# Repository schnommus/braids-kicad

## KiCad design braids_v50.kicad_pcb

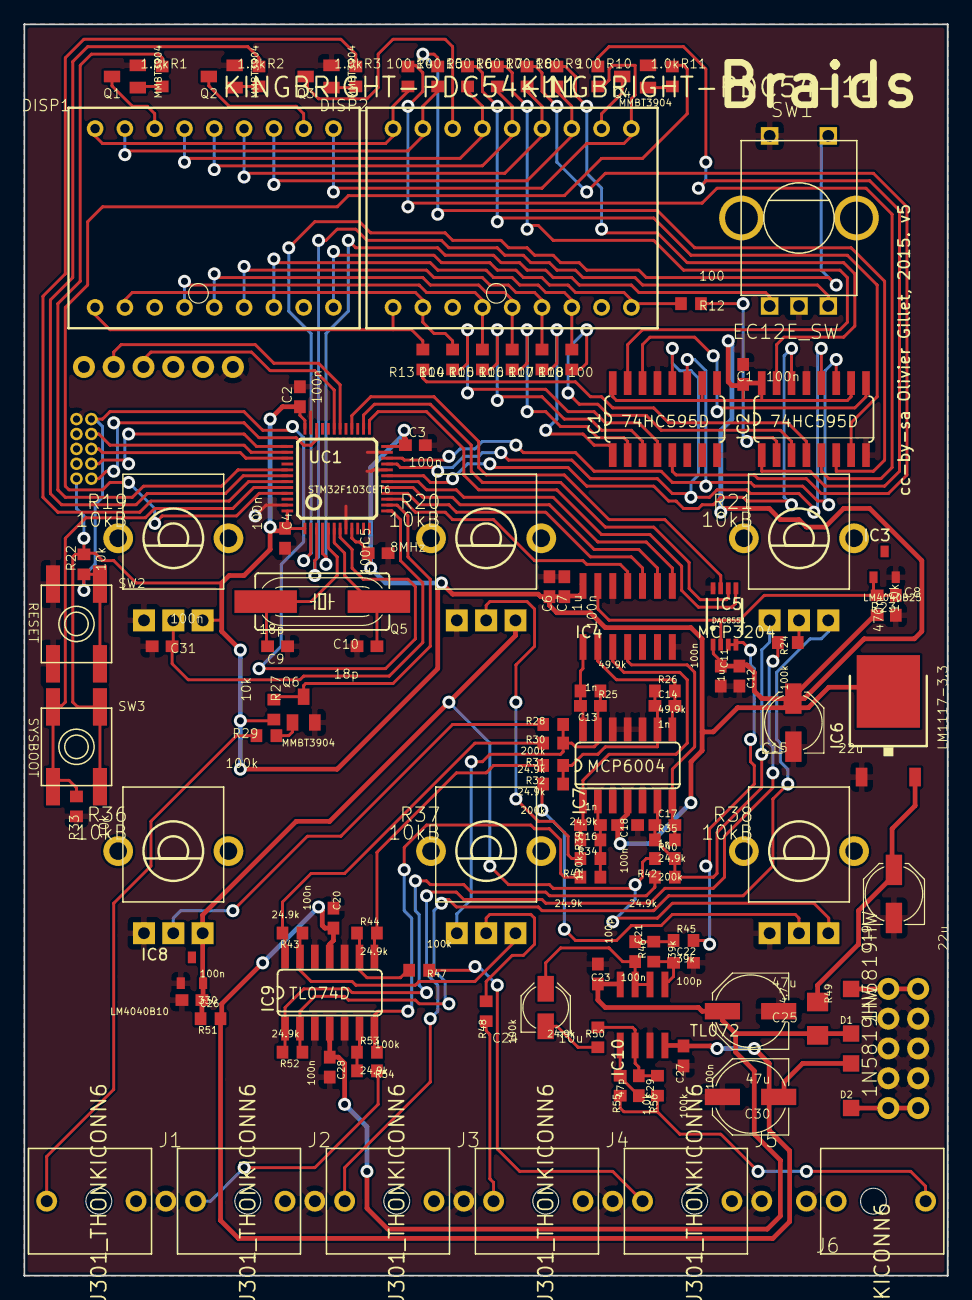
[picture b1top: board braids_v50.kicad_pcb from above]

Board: 2 copper layers, 78.7 x 106.7 mm, 120 parts (0 on the bottom side), 110 nets.

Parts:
C1, C2, C3, C4, C5, C7, C11, C18, C20, C23, C26, C27, C28, C31: 100n; C0603
C6, C12: 1u; C0603
C8: 470n; C0603
C9, C10: 18p; C0603
C13, C14, C16, C17: 1n; C0603
C15, C19: 22u; PANASONIC_C
C21, C22: 100p; C0603
C24: 10u; PANASONIC_B
C25, C30: 47u; PANASONIC_D
C29: 47p; C0603
D1, D2: 1N5819HW; SOD123
DISP1, DISP2: KINGBRIGHT-PDC54-11; PDC54
IC1, IC2: 74HC595D; SO16
IC3: LM4040B25; DBZ_R-PDSO-G3
IC4: MCP3204; SO14
IC5: DAC8551; MSOP-8
IC6: LM1117-3.3; TO252
IC7: MCP6004; SO14
IC8: LM4040B10; DBZ_R-PDSO-G3
IC9: TL074D; SO14
IC10: TL072; SO08
J1, J2, J3, J4, J5, J6: PJ301_THONKICONN6; WQP_PJ_301M6
JP1: M05X2PTH; AVR_ICSP
JP2: M05X2MINIJTAG; 2X5-1.27
JP3: 1X06
Q1, Q2, Q3, Q4, Q6: MMBT3904; SOT23-BEC
Q5: 8MHz; HC49UP
R1, R2, R3, R11, R23, R55: 1.0k; R0603
R4, R5, R6, R7, R8, R9, R10, R12, R13, R14, R15, R16, R17, R18: 100; R0603
R19, R20, R21, R36, R37, R38: 10kB; ALPS_POT_VERTICAL_PS
R22, R27, R33: 10k; R0603
R24, R29, R47, R48, R54, R56: 100k; R0603
R25, R26: 49.9k; R0603
R28, R32, R40: 200k; R0603
R30, R31, R34, R35, R41, R42, R43, R44, R50, R52, R53: 24.9k; R0603
R39: 120k; R0603
R45, R46: 39k; R0603
R49: 4.7; R1206
R51: 330; R0603
SW1: EC12E_SW; ALPS_EC12E_SW
SW2, SW3: EVQ-Q2
UC1: STM32F103CBT6; LQFP48

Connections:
+3V3: C1.1, C2.1, C3.1, C4.1, C5.1, C6.1, C7.1, C11.1, C12.1, C15.+, C18.1, IC1.10, IC1.16, IC2.10, IC2.16, IC4.14, IC5.1, IC6.3, IC7.4, JP2.1, R19.P$1, R22.2, R23.1, R27.2, SW3.B, SW3.B', UC1.1, UC1.9, UC1.24, UC1.36, UC1.48
/braids_v50_SS_1/ADC_MISO: IC4.10, UC1.16
/braids_v50_SS_1/ADC_MOSI: IC4.9, UC1.17
/braids_v50_SS_1/ADC_SCK: IC4.11, UC1.15
/braids_v50_SS_1/ADC_SS: IC4.8, UC1.18
/braids_v50_SS_1/BOOT_FLASH: R33.2, SW3.A, SW3.A', UC1.44
/braids_v50_SS_1/DAC_MOSI: IC5.7, UC1.28
/braids_v50_SS_1/DAC_SCK: IC5.6, UC1.26
/braids_v50_SS_1/DAC_SS: IC5.5, UC1.25
/braids_v50_SS_1/DISP_CHAR0: R3.1, UC1.43
/braids_v50_SS_1/DISP_CHAR1: R11.1, UC1.45
/braids_v50_SS_1/DISP_CHAR2: R1.1, UC1.41
/braids_v50_SS_1/DISP_CHAR3: R2.1, UC1.42
/braids_v50_SS_1/DISP_EN: IC1.12, IC2.12, UC1.21
/braids_v50_SS_1/DISP_SCK: IC1.11, IC2.11, UC1.22
/braids_v50_SS_1/DISP_SER: IC2.14, UC1.19
/braids_v50_SS_1/ENC_A: SW1.B, UC1.3
/braids_v50_SS_1/ENC_B: SW1.A, UC1.4
/braids_v50_SS_1/ENC_CLICK: SW1.E, UC1.2
/braids_v50_SS_1/FINE_TUNE: C31.1, R19.P$2, UC1.13
/braids_v50_SS_1/JTCK: JP2.4, UC1.37
/braids_v50_SS_1/JTDI: JP2.8, UC1.38
/braids_v50_SS_1/JTDO: JP2.6, UC1.39
/braids_v50_SS_1/JTMS: JP2.2, UC1.34
/braids_v50_SS_1/N$1: DISP2.16, Q3.C
/braids_v50_SS_1/N$2: DISP2.11, Q4.C
/braids_v50_SS_1/N$3: DISP1.16, Q1.C
/braids_v50_SS_1/N$4: DISP1.11, Q2.C
/braids_v50_SS_1/N$5: Q3.B, R3.2
/braids_v50_SS_1/N$6: Q4.B, R11.2
/braids_v50_SS_1/N$7: C9.2, Q5.2, UC1.5
/braids_v50_SS_1/N$8: C10.2, Q5.1, UC1.6
/braids_v50_SS_1/N$9: Q1.B, R1.2
/braids_v50_SS_1/N$10: Q2.B, R2.2
/braids_v50_SS_1/N$15: DISP1.12, DISP2.12, R9.2
/braids_v50_SS_1/N$16: DISP1.10, DISP2.10, R10.2
/braids_v50_SS_1/N$17: DISP1.9, DISP2.9, R12.2
/braids_v50_SS_1/N$18: DISP1.7, DISP2.7, R18.2
/braids_v50_SS_1/N$19: DISP1.1, DISP2.1, R13.2
/braids_v50_SS_1/N$20: DISP1.18, DISP2.18, R4.2
/braids_v50_SS_1/N$21: DISP1.17, DISP2.17, R5.2
/braids_v50_SS_1/N$22: DISP1.15, DISP2.15, R6.2
/braids_v50_SS_1/N$23: DISP1.14, DISP2.14, R7.2
/braids_v50_SS_1/N$24: DISP1.6, DISP2.6, R17.2
/braids_v50_SS_1/N$25: DISP1.5, DISP2.5, R16.2
/braids_v50_SS_1/N$26: DISP1.4, DISP2.4, R15.2
/braids_v50_SS_1/N$27: DISP1.2, DISP2.2, R14.2
/braids_v50_SS_1/N$28: DISP1.13, DISP2.13, R8.2
/braids_v50_SS_1/N$30: IC2.7, R6.1
/braids_v50_SS_1/N$31: IC1.14, IC2.9
/braids_v50_SS_1/N$32: IC2.15, R9.1
/braids_v50_SS_1/N$33: IC2.1, R10.1
/braids_v50_SS_1/N$34: IC2.2, R12.1
/braids_v50_SS_1/N$35: IC2.3, R18.1
/braids_v50_SS_1/N$36: IC2.4, R13.1
/braids_v50_SS_1/N$37: IC2.5, R4.1
/braids_v50_SS_1/N$38: IC2.6, R5.1
/braids_v50_SS_1/N$39: IC1.15, R7.1
/braids_v50_SS_1/N$40: IC1.1, R17.1
/braids_v50_SS_1/N$41: IC1.2, R16.1
/braids_v50_SS_1/N$42: IC1.3, R15.1
/braids_v50_SS_1/N$43: IC1.4, R14.1
/braids_v50_SS_1/N$44: IC1.5, R8.1
/braids_v50_SS_1/RESET: JP2.10, R22.1, SW2.B, SW2.B', UC1.7
/braids_v50_SS_1/RX: JP3.4, UC1.31
/braids_v50_SS_1/TX: JP3.5, UC1.30
/braids_v50_SS_2/N$12: IC9.7, R41.1, R53.2
/braids_v50_SS_2/N$13: R20.P$2, R39.1
/braids_v50_SS_2/N$14: J2.P3, R54.1
/braids_v50_SS_2/N$29: C16.1, IC7.2, R34.1, R39.2, R41.2
/braids_v50_SS_2/N$45: IC9.6, R53.1, R54.2
/braids_v50_SS_2/N$46: J3.P3, R24.1
/braids_v50_SS_2/N$47: J4.P3, R48.1
/braids_v50_SS_2/N$48: R21.P$2, R24.2
/braids_v50_SS_2/N$50: IC9.13, R37.P$1, R43.1
/braids_v50_SS_2/N$51: IC9.14, R30.1, R43.2
/braids_v50_SS_2/N$52: IC9.2, R21.P$1, R52.1
/braids_v50_SS_2/N$53: IC9.1, R42.1, R52.2
/braids_v50_SS_2/N$55: C17.1, IC7.6, R21.P$3, R35.1, R40.2, R42.2
/braids_v50_SS_2/N$57: J1.P3, R29.1
/braids_v50_SS_2/N$58: IC9.8, R31.1, R44.2
/braids_v50_SS_2/N$59: C13.1, IC7.13, R25.1, R28.2, R30.2, R37.P$3
/braids_v50_SS_2/N$60: J5.P3, R47.1
/braids_v50_SS_2/N$61: R28.1, R36.P$2
/braids_v50_SS_2/N$62: R37.P$2, R48.2
/braids_v50_SS_2/N$63: IC9.9, R44.1, R47.2
/braids_v50_SS_2/N$65: R32.1, R38.P$2
/braids_v50_SS_2/N$66: Q6.B, R29.2
/braids_v50_SS_2/N$67: C21.2, C24.+, IC10.6, IC10.7
/braids_v50_SS_2/N$68: C24.-, R50.2
/braids_v50_SS_2/N$69: C22.1, IC10.5, R46.1
/braids_v50_SS_2/N$70: C14.1, IC7.9, R26.1, R31.2, R32.2
/braids_v50_SS_2/N$71: C21.1, R45.1, R46.2
/braids_v50_SS_2/N$72: J6.P3, R55.1, R56.1
/braids_v50_SS_2/N$73: C29.2, IC10.1, R55.2
/braids_v50_SS_2/N$75: C29.1, IC10.2, R50.1, R56.2
/braids_v50_SS_3/N$49: C19.+, IC6.2, R49.1
/braids_v50_SS_3/N$56: D1.A, JP1.1, JP1.2
/braids_v50_SS_3/N$64: D2.C, JP1.9, JP1.10
AREF: C8.1, IC3.1, IC4.13, IC5.2, R23.2
AREF_-10: C26.1, IC8.2, R20.P$1, R36.P$1, R38.P$1, R40.1, R51.2
AUDIO_OUT: IC5.3, IC5.4, R45.2
FM_CV: C17.2, IC4.4, IC7.7, R35.2
GATE: Q6.C, R27.1, UC1.14
GND: C1.2, C2.2, C3.2, C4.2, C5.2, C6.2, C7.2, C8.2, C9.1, C10.1, C11.2, C12.2, C15.-, C18.2, C19.-, C20.1, C22.2, C23.2, C25.-, C26.2, C27.1, C28.2, C30.+, C31.2, IC1.8, IC1.13, IC2.8, IC2.13, IC3.2, IC4.7, IC4.12, IC5.8, IC6.1, IC7.3, IC7.5, IC7.10, IC7.11, IC7.12, IC8.1, IC9.3, IC9.5, IC9.10, IC9.12, IC10.3, J1.P1, J2.P1, J3.P1, J4.P1, J5.P1, J6.P1, JP1.3, JP1.4, JP1.5, JP1.6, JP1.7, JP1.8, JP2.3, JP2.5, JP2.9, JP3.1, Q1.E, Q2.E, Q3.E, Q4.E, Q6.E, R19.P$3, R20.P$3, R33.1, R36.P$3, R38.P$3, SW1.C, SW1.D, SW2.A, SW2.A', UC1.8, UC1.20, UC1.23, UC1.35, UC1.46, UC1.47
PARAM1_CV: C13.2, IC4.1, IC7.14, R25.2
PARAM2_CV: C14.2, IC4.2, IC7.8, R26.2
PITCH_CV: C16.2, IC4.3, IC7.1, R34.2
VCC: C23.1, C25.+, C28.1, D1.C, IC9.4, IC10.8, R49.2
VEE: C20.2, C27.2, C30.-, D2.A, IC9.11, IC10.4, R51.1

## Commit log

2017-07-23 Initial commit, groundplane is still broken
2017-07-23 Clean up incorrectly converted vias in prep to re-lay them

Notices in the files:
braids_v50.kicad_pcb:
cc-by-sa Olivier Gillet, 2015. v5
